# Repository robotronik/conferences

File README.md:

# Conférences

Dépôt avec les fichiers pour les conférences Phelma :

[Linux](linux/README.md)

[stm32]() lien à faire

[Asservissement](asservissements/README.md)

[Latex](latex/latex.md)

[Tutos](tutos/README.md)

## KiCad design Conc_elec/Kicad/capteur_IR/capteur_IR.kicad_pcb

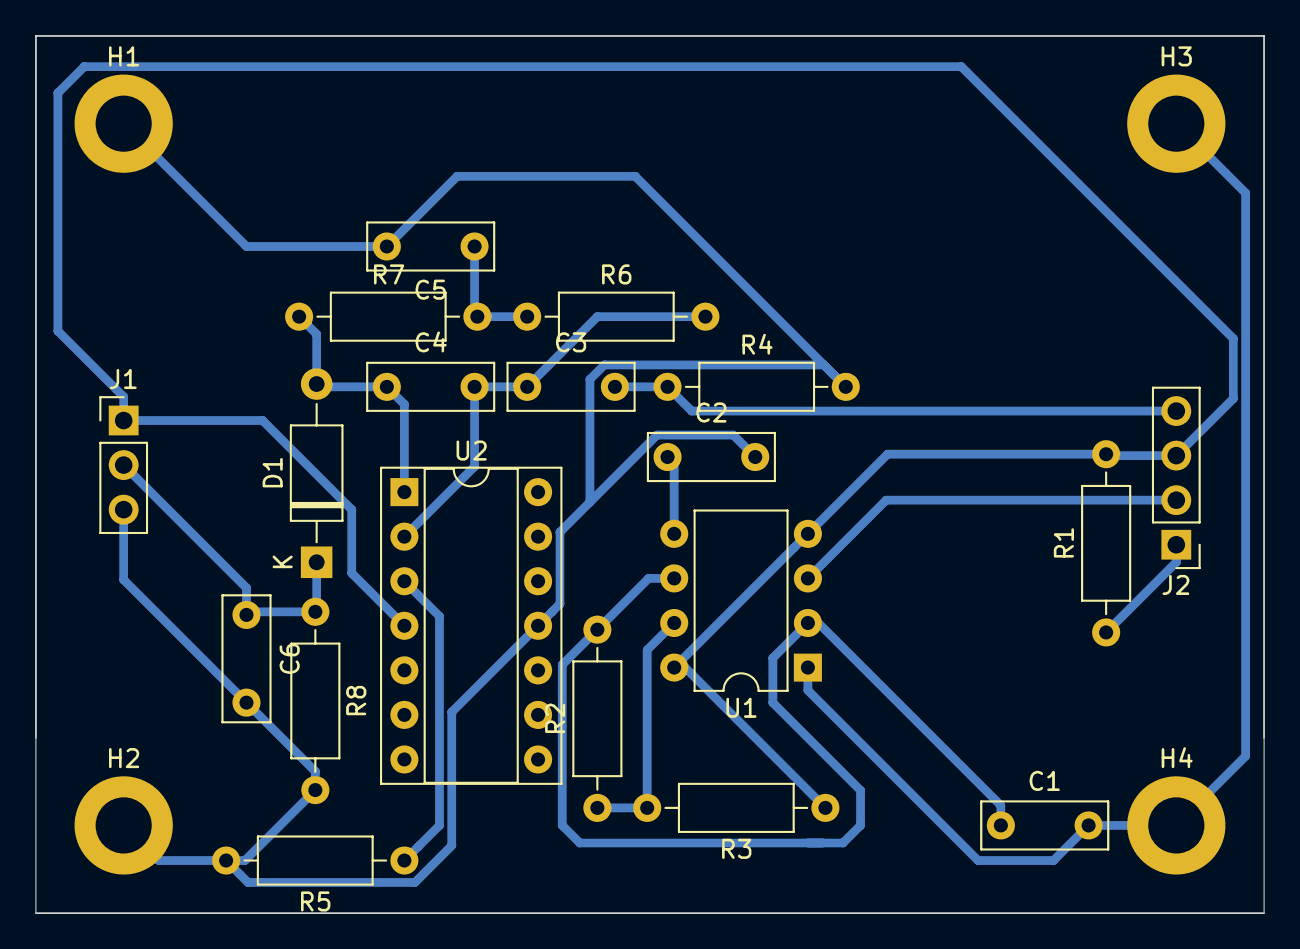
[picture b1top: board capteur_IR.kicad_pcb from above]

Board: 2 copper layers, 70.0 x 50.0 mm, 23 parts (0 on the bottom side), 13 nets.

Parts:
C1, C6: 10n; C_Rect_L7.0mm_W2.5mm_P5.00mm
C2: 100n; C_Rect_L7.0mm_W2.5mm_P5.00mm
C3, C5: 1u; C_Rect_L7.0mm_W2.5mm_P5.00mm
C4: 1n; C_Rect_L7.0mm_W2.5mm_P5.00mm
D1: D; D_A-405_P10.16mm_Horizontal
H1, H2, H3, H4: MountingHole_Pad; MountingHole_3.2mm_M3_DIN965_Pad
J1: Conn_01x03_Male; PinHeader_1x03_P2.54mm_Vertical
J2: Conn_01x04_Male; PinHeader_1x04_P2.54mm_Vertical
R1: 82; R_Axial_DIN0207_L6.3mm_D2.5mm_P10.16mm_Horizontal
R2: 6.8k; R_Axial_DIN0207_L6.3mm_D2.5mm_P10.16mm_Horizontal
R3: 2.7k; R_Axial_DIN0207_L6.3mm_D2.5mm_P10.16mm_Horizontal
R4: 510; R_Axial_DIN0207_L6.3mm_D2.5mm_P10.16mm_Horizontal
R5: 1k; R_Axial_DIN0207_L6.3mm_D2.5mm_P10.16mm_Horizontal
R6, R7: 33k; R_Axial_DIN0207_L6.3mm_D2.5mm_P10.16mm_Horizontal
R8: 39k; R_Axial_DIN0207_L6.3mm_D2.5mm_P10.16mm_Horizontal
U1: NE555; DIP-8_W7.62mm
U2: LM324; DIP-14_W7.62mm_Socket

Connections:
+5V: J1.1, J2.3, R1.2, R3.1, U1.4, U1.8, U2.4
C1: C6.1, D1.1, J1.2, R8.1
GND: C1.2, C2.2, C5.2, C6.2, H1.1, H2.1, H3.1, H4.1, J1.3, R4.2, R5.2, R8.2, U1.1, U2.11
unnamed: C1.1, R2.2, U1.2, U1.6
unnamed: C2.1, U1.5
unnamed: C3.1, C4.2, R6.2, U2.2
unnamed: C4.1, D1.2, R7.1, U2.1
unnamed: C5.1, R6.1, R7.2
unnamed: J2.1, R1.1
unnamed: R2.1, R3.2, U1.7
unnamed: R5.1, U2.3
em: J2.2, U1.3
rep: C3.2, J2.4, R4.1

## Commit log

2019-05-11 latex conf et linux conf
2019-05-13 edit linux.md & latex.md
2019-05-14 14/05/2019
2019-06-29 mise en dossier
2019-07-01 Linux conf in latex
2019-07-01 .gitignore
2019-07-01 gitignore entry
2019-07-01 linux : avancement Commande de bases
2019-07-02 Ajout makefile et avancement Introduction
2019-07-02 presentation
2019-07-06 tutos dir
2019-07-07 ajout tutos maintenir pc et install sdl phelma
2019-07-07 ajout de mes tutoriels sur la stm32
    version non définitives, il manque correction technique , orthographe , compréhension etc...
2019-07-10 ajout de précisions post correction de markdown
2019-07-10 test liens
2019-07-11 correction syntax markdown
2019-07-12 correction de md et ajout des photos dans bigboituto
2019-07-12 je stop de spam sur discord je promet
2019-07-15 Ajout des commandes de base
2019-07-22 add skeleton for presentation
2019-07-23 Continue stm32 presentation
2019-07-23 move data to content/
2019-07-23 split into files
2019-07-23 continue makefile
2019-07-24 ajout d'un readme pour le tuto stm
    des modifications sont a faire sur le readme afin de le rendre opérationnel. Il faut par exemple ajouter les liens vers les document pdf compilé ou encore ajouter les commande dinstallation des packe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
2019-07-28 finalisation de la première verison du tuto pipeline, prêt pour révision. modification et correction de syntaxe et expression generale
2019-08-01 adaptation tuto en .md et ajout commande
2019-08-01 ajout fichier
2019-08-01 modification images
2019-08-02 lien de retour au sommaire
2019-08-02 introduction premier jet
2019-08-29 Suite tuto stm32
2019-08-29 forgot to add files
2019-08-29 fix descr
2019-08-30 Conf LaTeX : sommaire, intros, et plan succint
2019-09-12 [linux] ajout explication path
2019-09-23 restart
2019-09-23 link fix
2019-09-23 matériel terminé
2019-09-26 Fix link asservissement
2019-09-26 Fix link latex
2019-10-15 debut conf elec
2019-10-15 version de ce soir (Sans KICAD)
2019-10-16 avec le PCB
2019-10-16 version 1
2019-10-16 ajout logo
2019-10-16 le logo degueu
2019-11-06 Linux presentation
2019-11-10 Conf linux
2019-11-10 distro_mosaic
2019-11-10 Avancement arborescence
2019-11-11 Conf v1
2019-11-12 presentation linux v2
2019-12-09 presentation git
2019-12-22 reduce images size
2020-02-09 add unfinished compilation conference
2020-02-09 Add first pages, tikz
2020-02-09 fix gitignore
2020-02-11 Fix latex imports, lstlistings config
2020-02-11 Finish compilation
2020-02-11 Almost finish buildtools
2020-02-11 Add section title frames
2020-02-11 move subsections as sections
2020-02-11 Start adding examples
2020-02-11 add build command in tex file
2020-02-12 cleanup legacy files
2020-02-12 remove useles files, move makefile
2020-02-12 Change date, add url
2020-02-12 Change exemples, add some text
2020-02-12 Change some things at the end of the presentation
2020-11-11 créé conferences/linux2020
2020-11-11 slides conf linux
2021-10-22 update PDF conception elec 2020
2021-10-22 pdf conception elec 2019
